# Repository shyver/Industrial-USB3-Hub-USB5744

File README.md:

# Industrial 4-Port USB 3.0 Hub (High-Speed Design)

## 📌 Project Overview
This repository contains the hardware design files for an industrial-grade, 4-port USB 3.0 (SuperSpeed 5Gbps) Hub. 

Designed around the **Microchip USB5744** hub controller, this project demonstrates advanced high-speed digital PCB design. It features a strict 4-layer stackup, precisely calculated 90Ω differential impedance routing, length-matching, robust ESD protection, and independent per-port power management. 

It is engineered to reliably convert a single USB-C upstream connection into four high-speed USB-A downstream ports in harsh or demanding environments.

*(Insert a screenshot of your routed PCB showing the differential pairs here later!)*

## ✨ Key Hardware Features
* **SuperSpeed Data (5 Gbps):** Full USB 3.1 Gen 1 compliance utilizing edge-coupled differential microstrip routing.
* **Impedance Control:** Mathematically calculated 90Ω differential impedance ($Z_{diff}$) tuned specifically for the JLC04161H-3313 manufacturing stackup.
* **Industrial Power Distribution:** Integrated power load switches providing dedicated, current-limited 5V power to each downstream port to prevent cascading short-circuit failures.
* **Heavy-Duty ESD Protection:** Ultra-low capacitance (< 0.5pF) TVS diode arrays on all SuperSpeed data lines to absorb transient voltage spikes without distorting multi-gigabit signal integrity.
* **Clean Clocking:** 25MHz external crystal oscillator with localized ground guarding to minimize EMI/Crosstalk.

## 📐 High-Speed PCB Specifications

To achieve reliable 5 Gbps data rates, standard 2-layer routing is insufficient. This board utilizes a custom 4-layer stackup to provide immediate, unbroken return paths for high-frequency signals.

* **Stackup Architecture:**
  * **Layer 1 (Top):** High-Speed Signals
  * **Layer 2 (In1):** Solid Ground Plane (Continuous Return Path)
  * **Layer 3 (In2):** Power Planes (5V, 3.3V, 1.2V)
  * **Layer 4 (Bottom):** Low-Speed Signals & Support Components
* **Impedance Math (USB 3.0 `SSTX`/`SSRX` & USB 2.0 `D+/D-`):**
  * Target Differential Impedance: **90 Ω ±10%**
  * Substrate Dielectric ($E_r$): **4.05**
  * Distance to Ground ($H$): **0.0964 mm**
  * Calculated Trace Width ($W$): **0.20 mm**
  * Calculated Trace Gap ($S$): **0.18 mm**

## 📂 Repository Structure
* `/Hardware` - KiCad 8.0 project files (`.kicad_sch`, `.kicad_pcb`).
* `/Docs` - Datasheets for the USB5744, Power Switches, and Ultra-low capacitance TVS diodes.
* `/Calculations` - Screenshots and data for the impedance and stackup calculations.
* `/Fabrication` - Gerber files, Drill files, BOM, and CPL files ready for PCBA.

## 🚀 Getting Started
1. Clone this repository: `git clone https://github.com/YourUsername/Industrial-USB3-Hub-USB5744.git`
2. Open the `.pro` or `.kicad_pro` file in **KiCad**.
3. *Note: Ensure your KiCad DRC rules are configured for the 4-layer constraints detailed above before modifying the layout.*

## 📝 License
This project is open-source and available under the [MIT License](LICENSE).

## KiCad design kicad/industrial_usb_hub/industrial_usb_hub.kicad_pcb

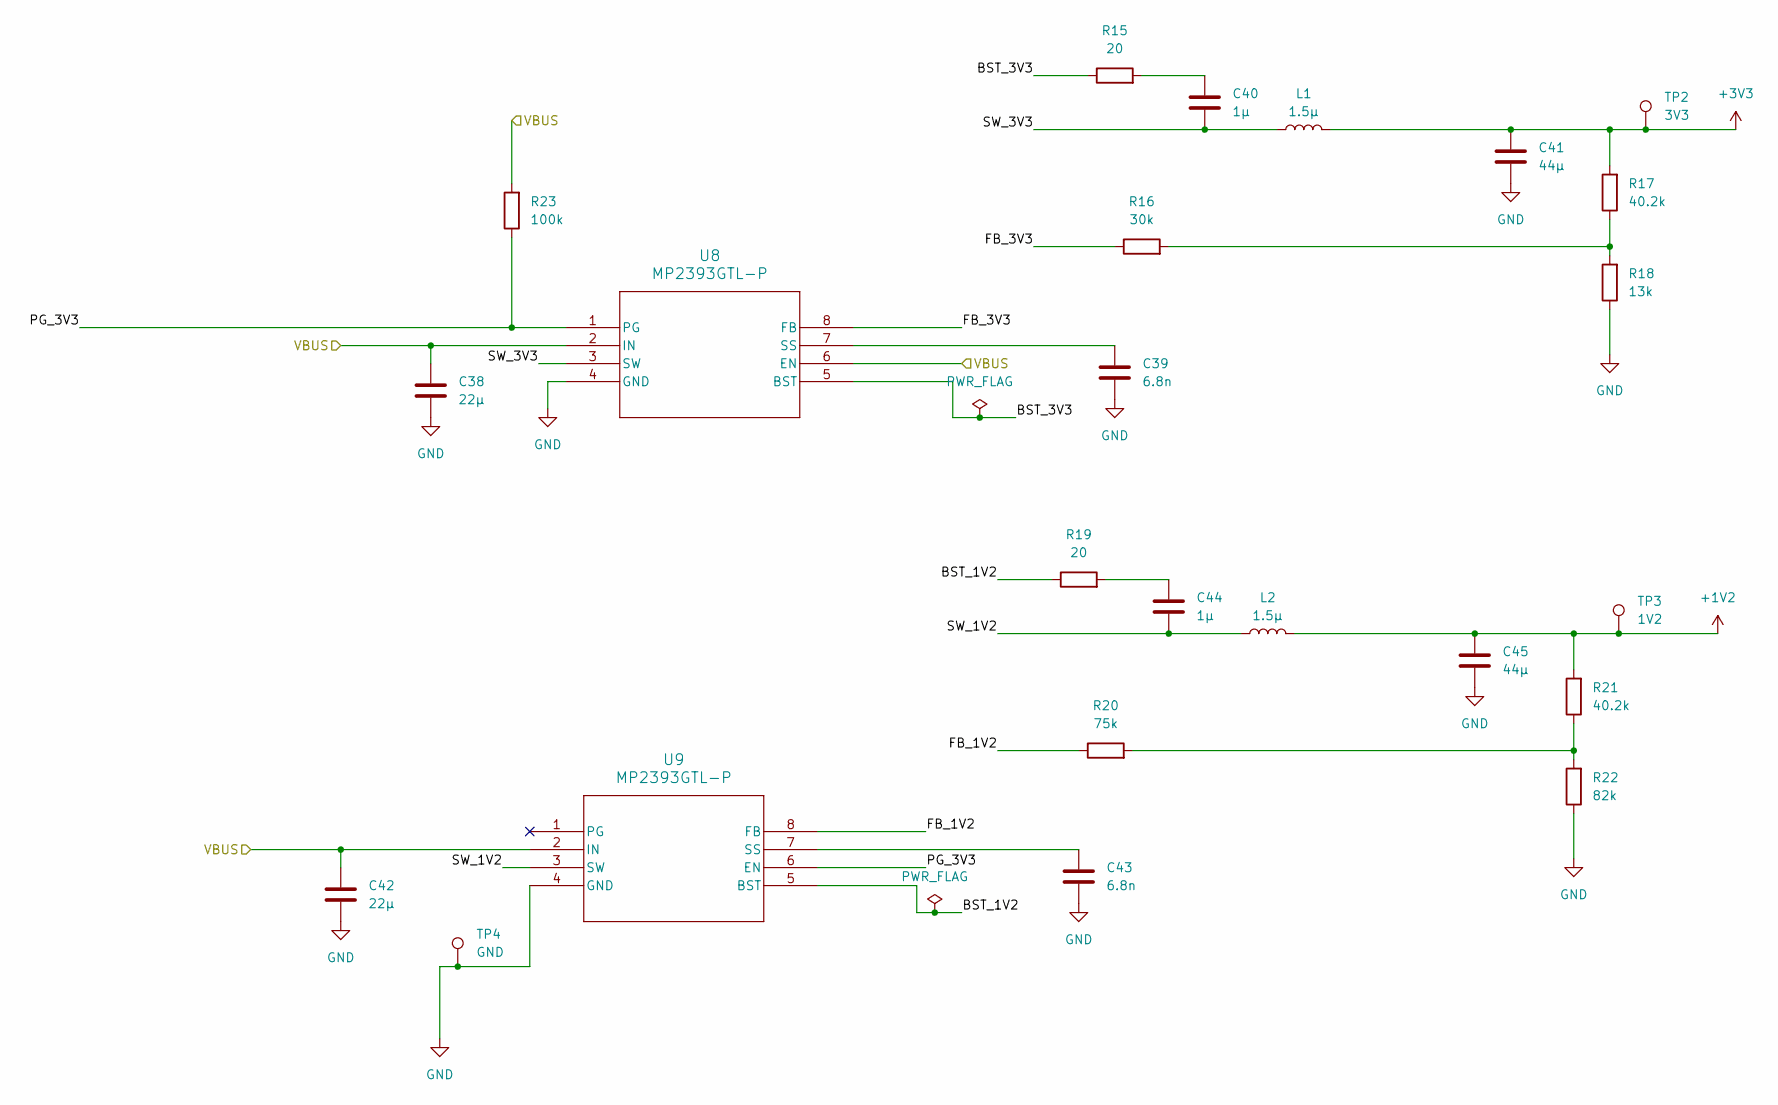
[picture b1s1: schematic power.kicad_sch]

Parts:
C38, C42: 22µ; C_0201_0603Metric
C39, C43: 6.8n; C_0201_0603Metric
C40, C44: 1µ; C_0201_0603Metric
C41, C45: 44µ; C_0201_0603Metric
L1, L2: 1.5µ; L_Taiyo-Yuden_NR-40xx
R15, R19: 20; R_0201_0603Metric
R16: 30k; R_0201_0603Metric
R17, R21: 40.2k; R_0201_0603Metric
R18: 13k; R_0201_0603Metric
R20: 75k; R_0201_0603Metric
R22: 82k; R_0201_0603Metric
R23: 100k; R_0201_0603Metric
TP2: 3V3; TestPoint_Pad_1.0x1.0mm
TP3: 1V2; TestPoint_Pad_1.0x1.0mm
TP4: GND; TestPoint_Pad_1.0x1.0mm
U8, U9: MP2393GTL-P; SOT583_MP2393

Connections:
+1V2: C45.1, L2.2, R21.2, TP3.1; also elsewhere on the board
+3V3: C41.1, L1.2, R17.2, TP2.1; also elsewhere on the board
/Downstream/VBUS: C38.1, C42.1, R23.2, U8.2 (IN), U8.6 (EN), U9.2 (IN); also elsewhere on the board
/Power/BST_1V2: R19.1, U9.5 (BST)
/Power/BST_3V3: R15.1, U8.5 (BST)
/Power/FB_1V2: R20.1, U9.8 (FB)
/Power/FB_3V3: R16.1, U8.8 (FB)
/Power/PG_3V3: R23.1, U8.1 (PG), U9.6 (EN)
/Power/SW_1V2: C44.2, L2.1, U9.3 (SW)
/Power/SW_3V3: C40.2, L1.1, U8.3 (SW)
GND: C38.2, C39.2, C41.2, C42.2, C43.2, C45.2, R18.1, R22.1, TP4.1, U8.4 (GND), U9.4 (GND); also elsewhere on the board
unnamed: C40.1, R15.2
unnamed: C44.1, R19.2
unnamed: R16.2, R17.1, R18.2
unnamed: R20.2, R21.1, R22.2
unnamed: C39.1, U8.7 (SS)
unnamed: C43.1, U9.7 (SS)

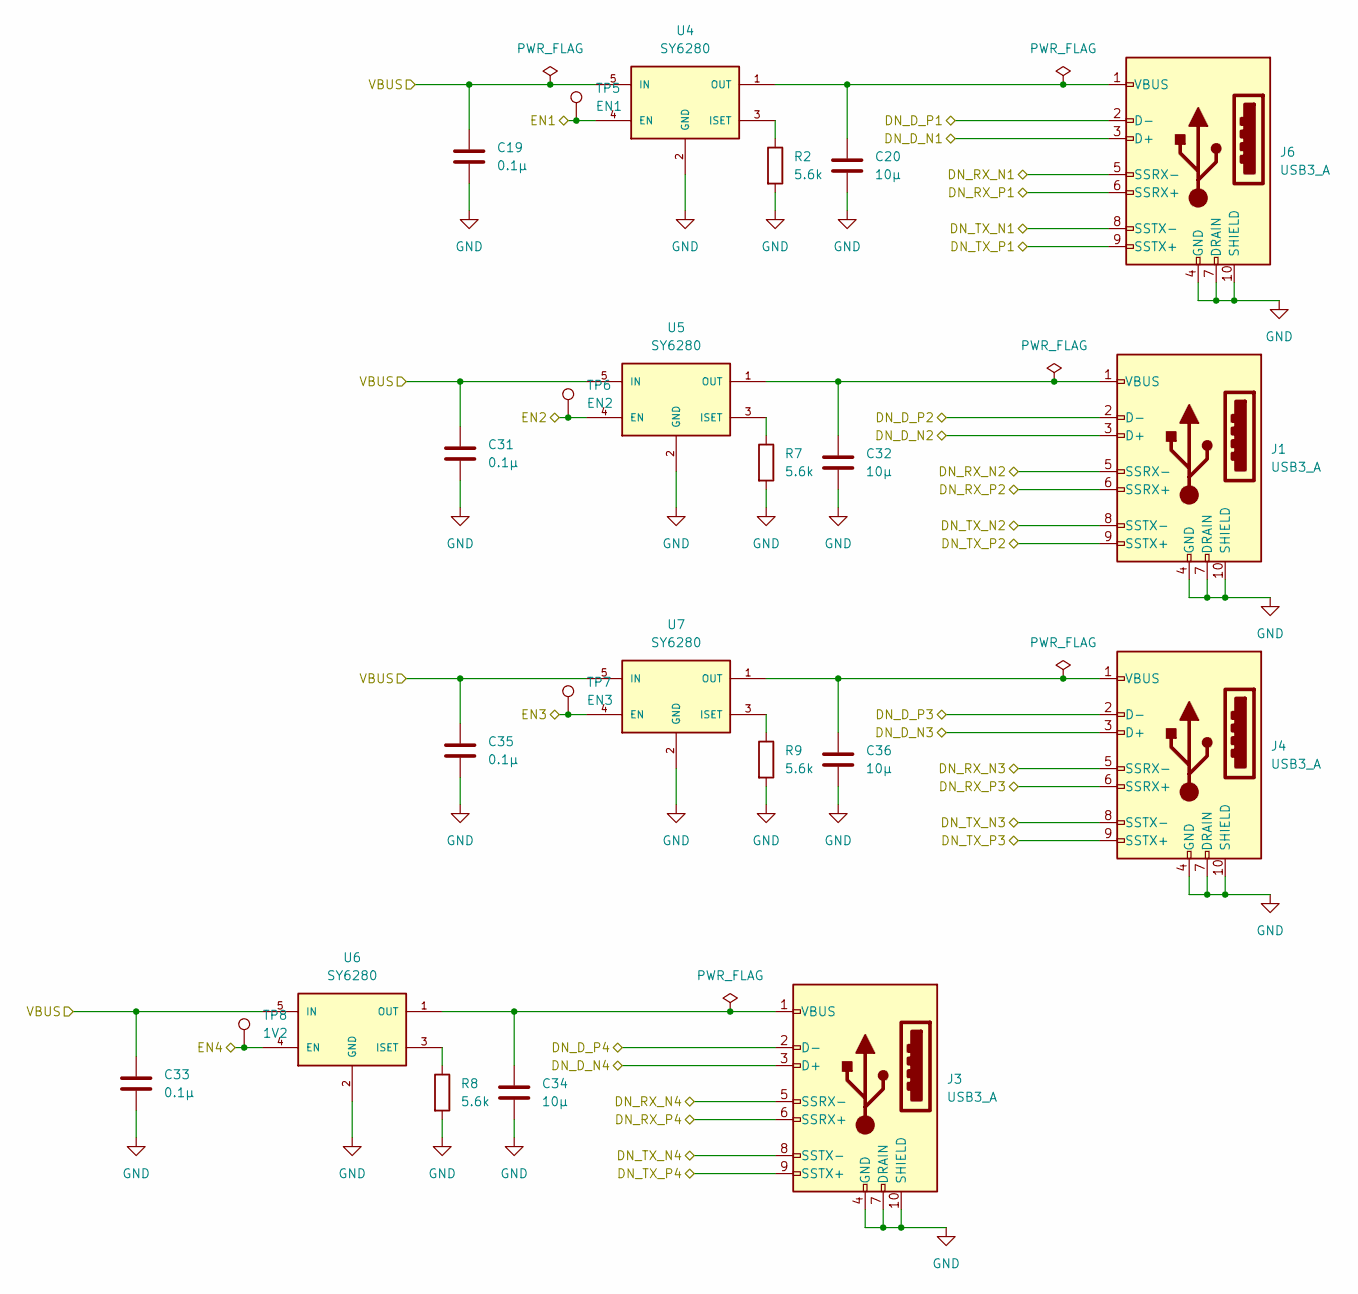
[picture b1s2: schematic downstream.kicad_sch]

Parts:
C19, C31, C33, C35: 0.1µ; C_0201_0603Metric
C20, C32, C34, C36: 10µ; C_0201_0603Metric
J1, J3, J4, J6: USB3_A; USB3_A_Molex_48393-001
R2, R7, R8, R9: 5.6k; R_0201_0603Metric
TP5: EN1; TestPoint_Pad_1.0x1.0mm
TP6: EN2; TestPoint_Pad_1.0x1.0mm
TP7: EN3; TestPoint_Pad_1.0x1.0mm
TP8: 1V2; TestPoint_Pad_1.0x1.0mm
U4, U5, U6, U7: SY6280; SOT23-5; PARTS SY6280

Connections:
/Downstream/DN_D_N1: J6.3 (D+); also elsewhere on the board
/Downstream/DN_D_N2: J1.3 (D+); also elsewhere on the board
/Downstream/DN_D_N3: J4.3 (D+); also elsewhere on the board
/Downstream/DN_D_N4: J3.3 (D+); also elsewhere on the board
/Downstream/DN_D_P1: J6.2 (D-); also elsewhere on the board
/Downstream/DN_D_P2: J1.2 (D-); also elsewhere on the board
/Downstream/DN_D_P3: J4.2 (D-); also elsewhere on the board
/Downstream/DN_D_P4: J3.2 (D-); also elsewhere on the board
/Downstream/DN_RX_N1: J6.5 (SSRX-); also elsewhere on the board
/Downstream/DN_RX_N2: J1.5 (SSRX-); also elsewhere on the board
/Downstream/DN_RX_N3: J4.5 (SSRX-); also elsewhere on the board
/Downstream/DN_RX_N4: J3.5 (SSRX-); also elsewhere on the board
/Downstream/DN_RX_P1: J6.6 (SSRX+); also elsewhere on the board
/Downstream/DN_RX_P2: J1.6 (SSRX+); also elsewhere on the board
/Downstream/DN_RX_P3: J4.6 (SSRX+); also elsewhere on the board
/Downstream/DN_RX_P4: J3.6 (SSRX+); also elsewhere on the board
/Downstream/DN_TX_N1: J6.8 (SSTX-); also elsewhere on the board
/Downstream/DN_TX_N2: J1.8 (SSTX-); also elsewhere on the board
/Downstream/DN_TX_N3: J4.8 (SSTX-); also elsewhere on the board
/Downstream/DN_TX_N4: J3.8 (SSTX-); also elsewhere on the board
/Downstream/DN_TX_P1: J6.9 (SSTX+); also elsewhere on the board
/Downstream/DN_TX_P2: J1.9 (SSTX+); also elsewhere on the board
/Downstream/DN_TX_P3: J4.9 (SSTX+); also elsewhere on the board
/Downstream/DN_TX_P4: J3.9 (SSTX+); also elsewhere on the board
/Downstream/EN1: TP5.1, U4.4 (EN); also elsewhere on the board
/Downstream/EN2: TP6.1, U5.4 (EN); also elsewhere on the board
/Downstream/EN3: TP7.1, U7.4 (EN); also elsewhere on the board
/Downstream/EN4: TP8.1, U6.4 (EN); also elsewhere on the board
/Downstream/VBUS: C19.2, C31.2, C33.2, C35.2, U4.5 (IN), U5.5 (IN), U6.5 (IN), U7.5 (IN); also elsewhere on the board
GND: C19.1, C20.1, C31.1, C32.1, C33.1, C34.1, C35.1, C36.1, J1.4 (GND), J1.7 (DRAIN), J1.10 (SHIELD), J3.4 (GND), J3.7 (DRAIN), J3.10 (SHIELD), J4.4 (GND), J4.7 (DRAIN), J4.10 (SHIELD), J6.4 (GND), J6.7 (DRAIN), J6.10 (SHIELD), R2.2, R7.2, R8.2, R9.2, U4.2 (GND), U5.2 (GND), U6.2 (GND), U7.2 (GND); also elsewhere on the board
unnamed: C32.2, J1.1 (VBUS), U5.1 (OUT)
unnamed: C34.2, J3.1 (VBUS), U6.1 (OUT)
unnamed: C36.2, J4.1 (VBUS), U7.1 (OUT)
unnamed: C20.2, J6.1 (VBUS), U4.1 (OUT)
unnamed: R2.1, U4.3 (ISET)
unnamed: R7.1, U5.3 (ISET)
unnamed: R8.1, U6.3 (ISET)
unnamed: R9.1, U7.3 (ISET)

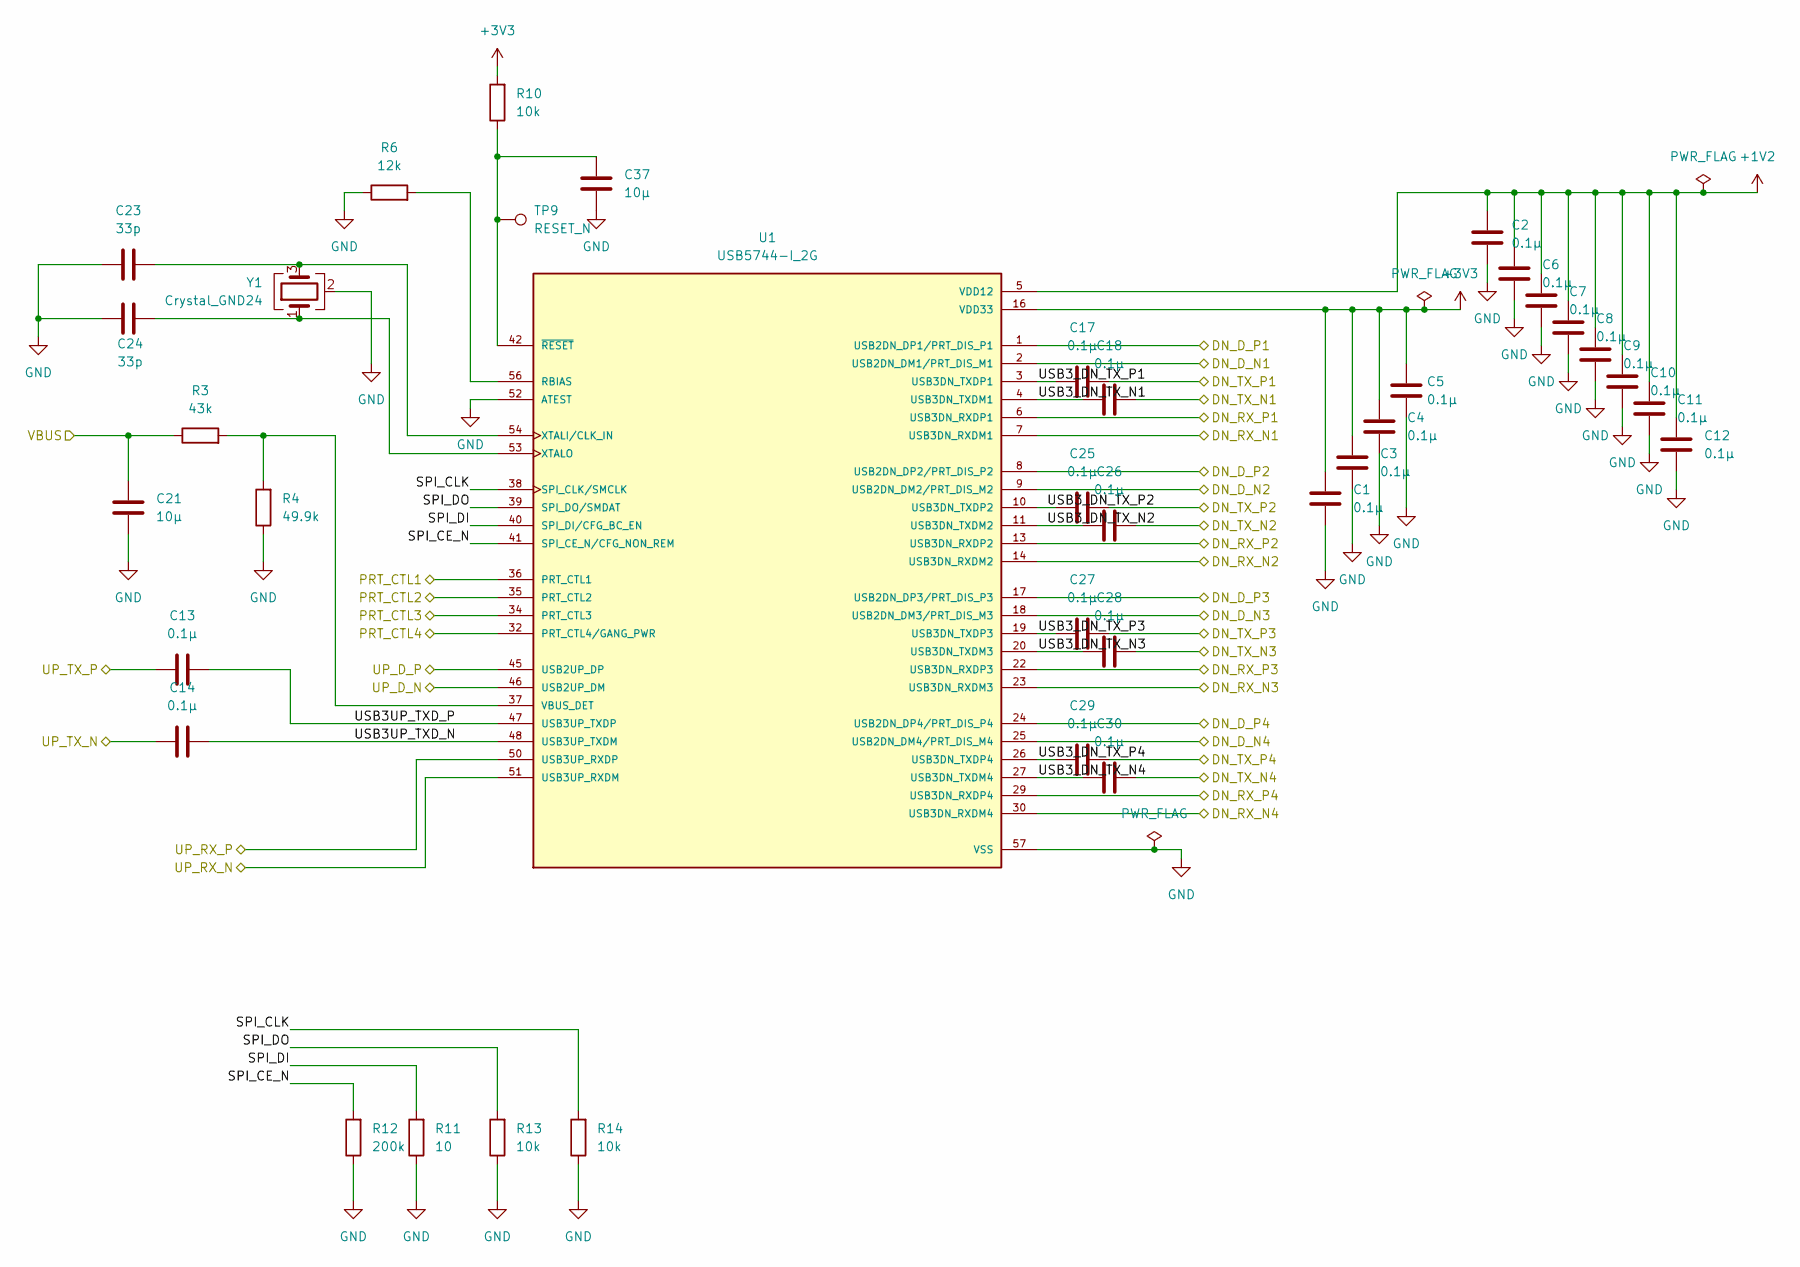
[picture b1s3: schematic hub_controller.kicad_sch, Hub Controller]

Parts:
C1, C2, C3, C4, C5, C6, C7, C8, C9, C10, C11, C12, C13, C14, C17, C18, C25, C26, C27, C28, C29, C30: 0.1µ; C_0201_0603Metric
C21, C37: 10µ; C_0201_0603Metric
C23, C24: 33p; C_0201_0603Metric
R3: 43k; R_0201_0603Metric
R4: 49.9k; R_0201_0603Metric
R6: 12k; R_0201_0603Metric
R10, R13, R14: 10k; R_0201_0603Metric
R11: 10; R_0201_0603Metric
R12: 200k; R_0201_0603Metric
TP9: RESET_N; TestPoint_Pad_1.0x1.0mm
U1: USB5744-I_2G; USB5744-QFN40P700X700X100-57N; PARTREV DS00001855J
Y1: Crystal_GND24; 403I35D25M00000

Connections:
+1V2: C2.1, C6.1, C7.1, C8.1, C9.1, C10.1, C11.1, C12.1, U1.5 (VDD12), U1.12 (VDD12), U1.15 (VDD12), U1.21 (VDD12), U1.28 (VDD12), U1.33 (VDD12), U1.43 (VDD12), U1.49 (VDD12); also elsewhere on the board
+3V3: C1.1, C3.1, C4.1, C5.1, R10.2, U1.16 (VDD33), U1.31 (VDD33), U1.44 (VDD33), U1.55 (VDD33); also elsewhere on the board
/Downstream/DN_D_N1: U1.2 (USB2DN_DM1/PRT_DIS_M1); also elsewhere on the board
/Downstream/DN_D_N2: U1.9 (USB2DN_DM2/PRT_DIS_M2); also elsewhere on the board
/Downstream/DN_D_N3: U1.18 (USB2DN_DM3/PRT_DIS_M3); also elsewhere on the board
/Downstream/DN_D_N4: U1.25 (USB2DN_DM4/PRT_DIS_M4); also elsewhere on the board
/Downstream/DN_D_P1: U1.1 (USB2DN_DP1/PRT_DIS_P1); also elsewhere on the board
/Downstream/DN_D_P2: U1.8 (USB2DN_DP2/PRT_DIS_P2); also elsewhere on the board
/Downstream/DN_D_P3: U1.17 (USB2DN_DP3/PRT_DIS_P3); also elsewhere on the board
/Downstream/DN_D_P4: U1.24 (USB2DN_DP4/PRT_DIS_P4); also elsewhere on the board
/Downstream/DN_RX_N1: U1.7 (USB3DN_RXDM1); also elsewhere on the board
/Downstream/DN_RX_N2: U1.14 (USB3DN_RXDM2); also elsewhere on the board
/Downstream/DN_RX_N3: U1.23 (USB3DN_RXDM3); also elsewhere on the board
/Downstream/DN_RX_N4: U1.30 (USB3DN_RXDM4); also elsewhere on the board
/Downstream/DN_RX_P1: U1.6 (USB3DN_RXDP1); also elsewhere on the board
/Downstream/DN_RX_P2: U1.13 (USB3DN_RXDP2); also elsewhere on the board
/Downstream/DN_RX_P3: U1.22 (USB3DN_RXDP3); also elsewhere on the board
/Downstream/DN_RX_P4: U1.29 (USB3DN_RXDP4); also elsewhere on the board
/Downstream/DN_TX_N1: C18.2; also elsewhere on the board
/Downstream/DN_TX_N2: C26.2; also elsewhere on the board
/Downstream/DN_TX_N3: C28.2; also elsewhere on the board
/Downstream/DN_TX_N4: C30.2; also elsewhere on the board
/Downstream/DN_TX_P1: C17.2; also elsewhere on the board
/Downstream/DN_TX_P2: C25.2; also elsewhere on the board
/Downstream/DN_TX_P3: C27.2; also elsewhere on the board
/Downstream/DN_TX_P4: C29.2; also elsewhere on the board
/Downstream/EN1: U1.36 (PRT_CTL1); also elsewhere on the board
/Downstream/EN2: U1.35 (PRT_CTL2); also elsewhere on the board
/Downstream/EN3: U1.34 (PRT_CTL3); also elsewhere on the board
/Downstream/EN4: U1.32 (PRT_CTL4/GANG_PWR); also elsewhere on the board
/Downstream/VBUS: C21.2, R3.1; also elsewhere on the board
/Hub Controller/SPI_CE_N: R12.2, U1.41 (SPI_CE_N/CFG_NON_REM)
/Hub Controller/SPI_CLK: R14.2, U1.38 (SPI_CLK/SMCLK)
/Hub Controller/SPI_DI: R11.2, U1.40 (SPI_DI/CFG_BC_EN)
/Hub Controller/SPI_DO: R13.2, U1.39 (SPI_DO/SMDAT)
/Hub Controller/UP_D_N: U1.46 (USB2UP_DM); also elsewhere on the board
/Hub Controller/UP_D_P: U1.45 (USB2UP_DP); also elsewhere on the board
/Hub Controller/UP_RX_N: U1.51 (USB3UP_RXDM); also elsewhere on the board
/Hub Controller/UP_RX_P: U1.50 (USB3UP_RXDP); also elsewhere on the board
/Hub Controller/UP_TX_N: C14.1; also elsewhere on the board
/Hub Controller/UP_TX_P: C13.1; also elsewhere on the board
/Hub Controller/USB3UP_TXD_N: C14.2, U1.48 (USB3UP_TXDM)
/Hub Controller/USB3UP_TXD_P: C13.2, U1.47 (USB3UP_TXDP)
/Hub Controller/USB3_DN_TX_N1: C18.1, U1.4 (USB3DN_TXDM1)
/Hub Controller/USB3_DN_TX_N2: C26.1, U1.11 (USB3DN_TXDM2)
/Hub Controller/USB3_DN_TX_N3: C28.1, U1.20 (USB3DN_TXDM3)
/Hub Controller/USB3_DN_TX_N4: C30.1, U1.27 (USB3DN_TXDM4)
/Hub Controller/USB3_DN_TX_P1: C17.1, U1.3 (USB3DN_TXDP1)
/Hub Controller/USB3_DN_TX_P2: C25.1, U1.10 (USB3DN_TXDP2)
/Hub Controller/USB3_DN_TX_P3: C27.1, U1.19 (USB3DN_TXDP3)
/Hub Controller/USB3_DN_TX_P4: C29.1, U1.26 (USB3DN_TXDP4)
GND: C1.2, C2.2, C3.2, C4.2, C5.2, C6.2, C7.2, C8.2, C9.2, C10.2, C11.2, C12.2, C21.1, C23.2, C24.2, C37.1, R4.1, R6.1, R11.1, R12.1, R13.1, R14.1, U1.52 (ATEST), U1.57 (VSS), Y1.2 (G), Y1.4 (G); also elsewhere on the board
unnamed: R6.2, U1.56 (RBIAS)
unnamed: R3.2, R4.2, U1.37 (VBUS_DET)
unnamed: C23.1, U1.54 (XTALI/CLK_IN), Y1.3
unnamed: C24.1, U1.53 (XTALO), Y1.1
unnamed: C37.2, R10.1, TP9.1, U1.42 (~RESET)

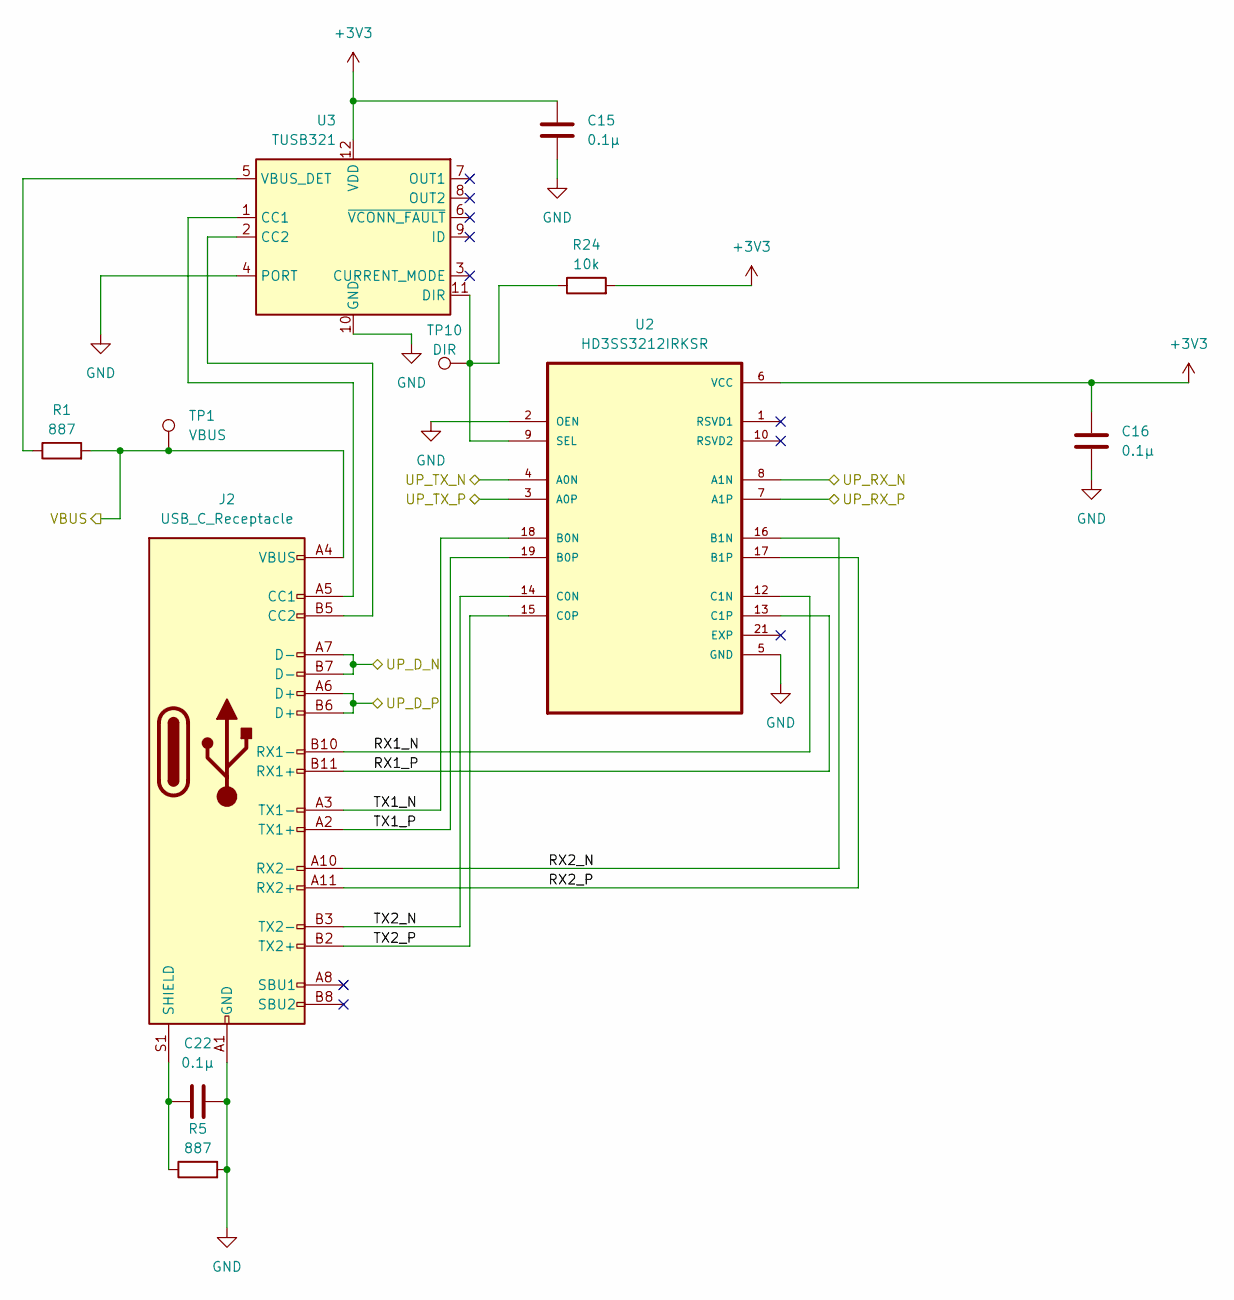
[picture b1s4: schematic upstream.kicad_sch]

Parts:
C15, C16, C22: 0.1µ; C_0201_0603Metric
J2: USB_C_Receptacle; BELFUSE_SS-52400-003
R1, R5: 887; R_0201_0603Metric
R24: 10k; R_0201_0603Metric
TP1: VBUS; TestPoint_Pad_1.0x1.0mm
TP10: DIR; TestPoint_Pad_1.0x1.0mm
U2: HD3SS3212IRKSR; QFN50P450X250X100-21N
U3: TUSB321; Texas_X2QFN-12_1.6x1.6mm_P0.4mm

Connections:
+3V3: C15.1, C16.1, R24.2, U2.6 (VCC), U3.12 (VDD); also elsewhere on the board
/Downstream/VBUS: J2.A4 (VBUS), J2.A9 (VBUS), J2.B4 (VBUS), J2.B9 (VBUS), R1.2, TP1.1; also elsewhere on the board
/Hub Controller/UP_D_N: J2.A7 (D-), J2.B7 (D-); also elsewhere on the board
/Hub Controller/UP_D_P: J2.A6 (D+), J2.B6 (D+); also elsewhere on the board
/Hub Controller/UP_RX_N: U2.8 (A1N); also elsewhere on the board
/Hub Controller/UP_RX_P: U2.7 (A1P); also elsewhere on the board
/Hub Controller/UP_TX_N: U2.4 (A0N); also elsewhere on the board
/Hub Controller/UP_TX_P: U2.3 (A0P); also elsewhere on the board
/Upstream/RX1_N: J2.B10 (RX1-), U2.12 (C1N)
/Upstream/RX1_P: J2.B11 (RX1+), U2.13 (C1P)
/Upstream/RX2_N: J2.A10 (RX2-), U2.16 (B1N)
/Upstream/RX2_P: J2.A11 (RX2+), U2.17 (B1P)
/Upstream/TX1_N: J2.A3 (TX1-), U2.18 (B0N)
/Upstream/TX1_P: J2.A2 (TX1+), U2.19 (B0P)
/Upstream/TX2_N: J2.B3 (TX2-), U2.14 (C0N)
/Upstream/TX2_P: J2.B2 (TX2+), U2.15 (C0P)
EXP: U2.21 (EXP)
GND: C15.2, C16.2, C22.2, J2.A1 (GND), J2.A12 (GND), J2.B1 (GND), J2.B12 (GND), R5.2, U2.2 (OEN), U2.5 (GND), U2.11 (GND), U2.20 (GND), U3.4 (PORT), U3.10 (GND); also elsewhere on the board
unnamed: J2.A5 (CC1), U3.1 (CC1)
unnamed: J2.B5 (CC2), U3.2 (CC2)
unnamed: C22.1, J2.S1 (SHIELD), R5.1
unnamed: R24.1, TP10.1, U2.9 (SEL), U3.11 (DIR)
unnamed: R1.1, U3.5 (VBUS_DET)

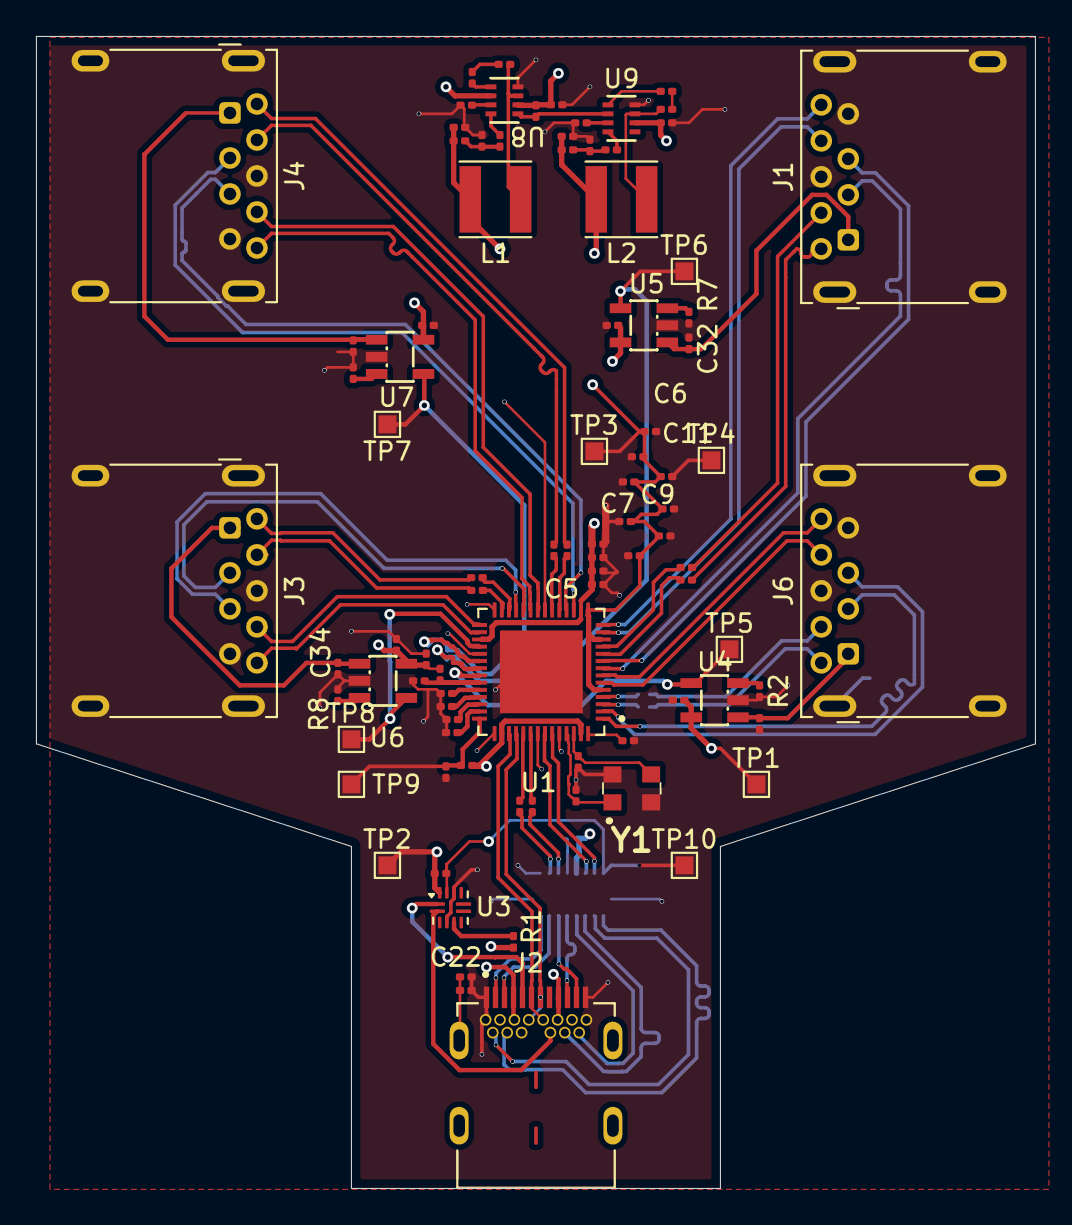
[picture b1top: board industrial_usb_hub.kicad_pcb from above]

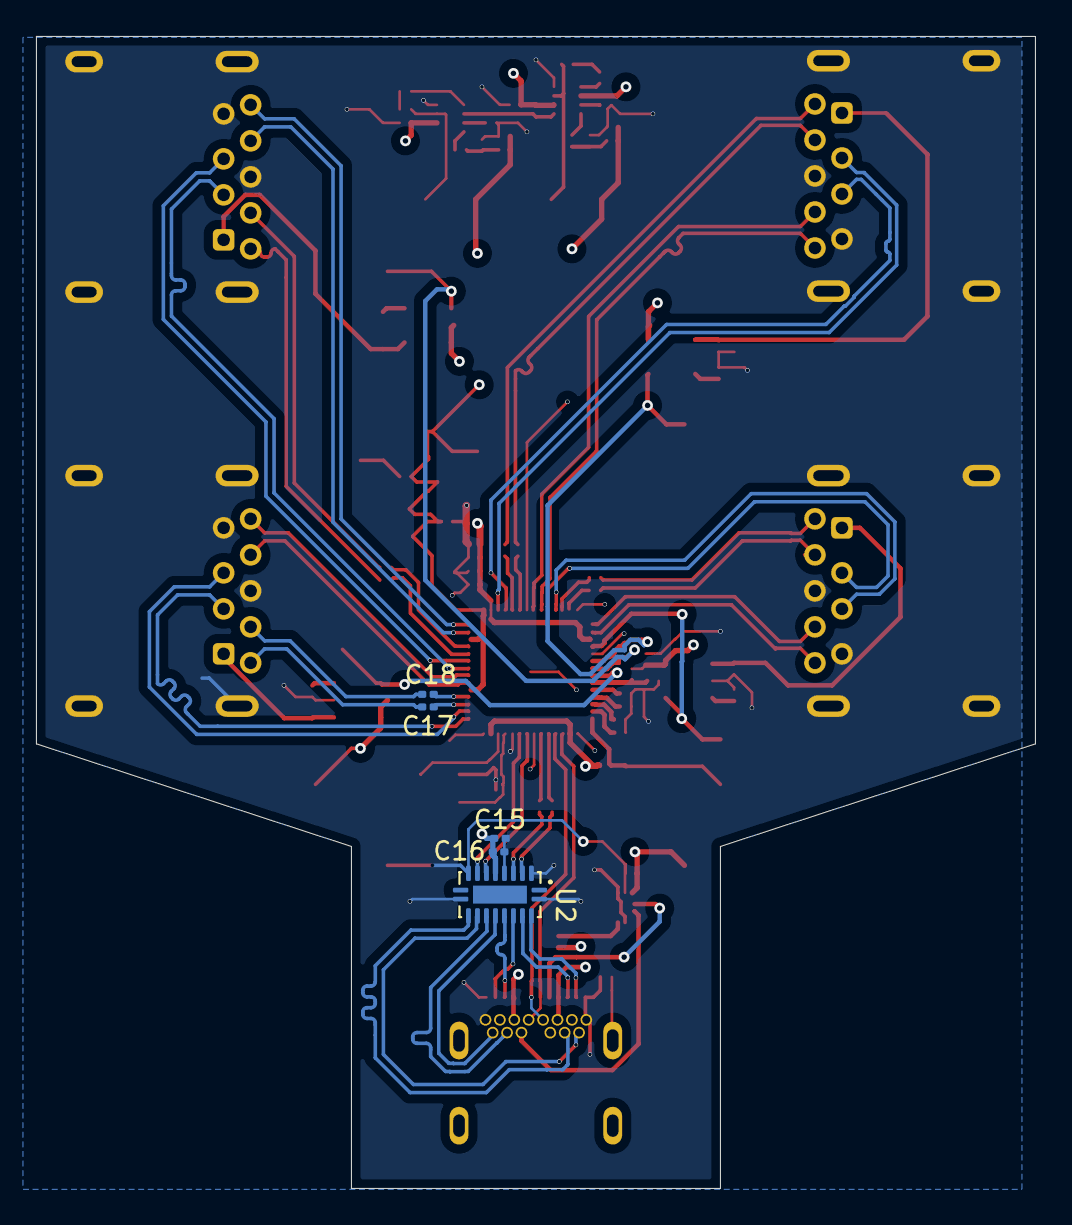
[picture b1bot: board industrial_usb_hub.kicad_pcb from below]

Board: 4 copper layers, 55.5 x 64.0 mm, 96 parts (5 on the bottom side), 91 nets.

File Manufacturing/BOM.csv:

"Reference","Qty","Value","DNP","Exclude from BOM","Exclude from Board","Footprint","Datasheet"
"C1,C2,C3,C4,C5,C6,C7,C8,C9,C10,C11,C12,C13,C14,C15,C16,C17,C18,C19,C22,C25,C26,C27,C28,C29,C30,C31,C33,C35","29","0.1µ","","","","Capacitor_SMD:C_0201_0603Metric","~"
"C20,C21,C32,C34,C36,C37","6","10µ","","","","Capacitor_SMD:C_0201_0603Metric","~"
"C23,C24","2","33p","","","","Capacitor_SMD:C_0201_0603Metric","~"
"C38,C42","2","22µ","","","","Capacitor_SMD:C_0201_0603Metric","~"
"C39,C43","2","6.8n","","","","Capacitor_SMD:C_0201_0603Metric","~"
"C40,C44","2","1µ","","","","Capacitor_SMD:C_0201_0603Metric","~"
"C41,C45","2","44µ","","","","Capacitor_SMD:C_0201_0603Metric","~"
"H1,H2","2","MountingHole_Pad","","Excluded from BOM","","MountingHole:MountingHole_3.2mm_M3_Pad_Via","~"
"J1,J3,J4,J6","4","USB3_A","","","","Connector_USB:USB3_A_Molex_48393-001","~"
"J2","1","USB_C_Receptacle","","","","personal_library:BELFUSE_SS-52400-003","https://www.usb.org/sites/default/files/documents/usb_type-c.zip"
"L1,L2","2","1.5µ","","","","Inductor_SMD:L_Taiyo-Yuden_NR-40xx","~"
"R1,R5","2","887","","","","Resistor_SMD:R_0201_0603Metric","~"
"R2,R7,R8,R9","4","5.6k","","","","Resistor_SMD:R_0201_0603Metric","~"
"R3","1","43k","","","","Resistor_SMD:R_0201_0603Metric","~"
"R4","1","49.9k","","","","Resistor_SMD:R_0201_0603Metric","~"
"R6","1","12k","","","","Resistor_SMD:R_0201_0603Metric","~"
"R10,R13,R14,R24","4","10k","","","","Resistor_SMD:R_0201_0603Metric","~"
"R11","1","10","","","","Resistor_SMD:R_0201_0603Metric","~"
"R12","1","200k","","","","Resistor_SMD:R_0201_0603Metric","~"
"R15,R19","2","20","","","","Resistor_SMD:R_0201_0603Metric","~"
"R16","1","30k","","","","Resistor_SMD:R_0201_0603Metric","~"
"R17,R21","2","40.2k","","","","Resistor_SMD:R_0201_0603Metric","~"
"R18","1","13k","","","","Resistor_SMD:R_0201_0603Metric","~"
"R20","1","75k","","","","Resistor_SMD:R_0201_0603Metric","~"
"R22","1","82k","","","","Resistor_SMD:R_0201_0603Metric","~"
"R23","1","100k","","","","Resistor_SMD:R_0201_0603Metric","~"
"TP1","1","VBUS","","","","TestPoint:TestPoint_Pad_1.0x1.0mm","~"
"TP2","1","3V3","","","","TestPoint:TestPoint_Pad_1.0x1.0mm","~"
"TP3,TP8","2","1V2","","","","TestPoint:TestPoint_Pad_1.0x1.0mm","~"
"TP4","1","GND","","","","TestPoint:TestPoint_Pad_1.0x1.0mm","~"
"TP5","1","EN1","","","","TestPoint:TestPoint_Pad_1.0x1.0mm","~"
"TP6","1","EN2","","","","TestPoint:TestPoint_Pad_1.0x1.0mm","~"
"TP7","1","EN3","","","","TestPoint:TestPoint_Pad_1.0x1.0mm","~"
"TP9","1","RESET_N","","","","TestPoint:TestPoint_Pad_1.0x1.0mm","~"
"TP10","1","DIR","","","","TestPoint:TestPoint_Pad_1.0x1.0mm","~"
"U1","1","USB5744-I_2G","","","","personal_library:USB5744-QFN40P700X700X100-57N",""
"U2","1","HD3SS3212IRKSR","","","","personal_library:QFN50P450X250X100-21N",""
"U3","1","TUSB321","","","","Package_DFN_QFN:Texas_X2QFN-12_1.6x1.6mm_P0.4mm","http://www.ti.com/lit/ds/symlink/tusb321.pdf"
"U4,U5,U6,U7","4","SY6280","","","","personal_library:SOT23-5",""
"U8,U9","2","MP2393GTL-P","","","","MP2393GTL-P:SOT583_MP2393","https://www.monolithicpower.com/en/documentview/productdocum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"
"Y1","1","Crystal_GND24","","","","personal_library:403I35D25M00000","~"

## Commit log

2026-04-01 initiated project, configured board, created some sheets in the schematic
2026-04-01 Add MIT License to the project
2026-04-10 completed upstream circuit, moving on to power and downstream
2026-04-11 completed schematic
2026-04-11 assigned footprints
2026-04-12 moved on to pcb editor, chose component placements, groups, now needs routing, and bro routing superspeed just sucks
2026-04-14 routed the USB C cables, fuck that was annoying, but at some point it just, got easier randomly? at an instant, didn't even notice it
2026-04-14 okay okay it seems easier to do differential routing, feels menacing tho
2026-04-15 done routing, now fixing DRC errors (it's hatin)
2026-04-15 finalized routing, fixed DRC issues, imported the 3D models, all good
2026-04-15 added testpoints
2026-04-15 Rename drill.zip to Manufacturing/drill.zip
2026-04-15 Rename BOM.csv to Manufacturing/BOM.csv
2026-04-15 Rename gerbers.zip to Manufacturing/gerbers.zip
2026-04-15 Rename pos.zip to Manufacturing/pos.zip
2026-04-15 Create README.md for USB 3.0 Hub project
    Added detailed project overview, specifications, and repository structure for the Industrial 4-Port USB 3.0 Hub.
